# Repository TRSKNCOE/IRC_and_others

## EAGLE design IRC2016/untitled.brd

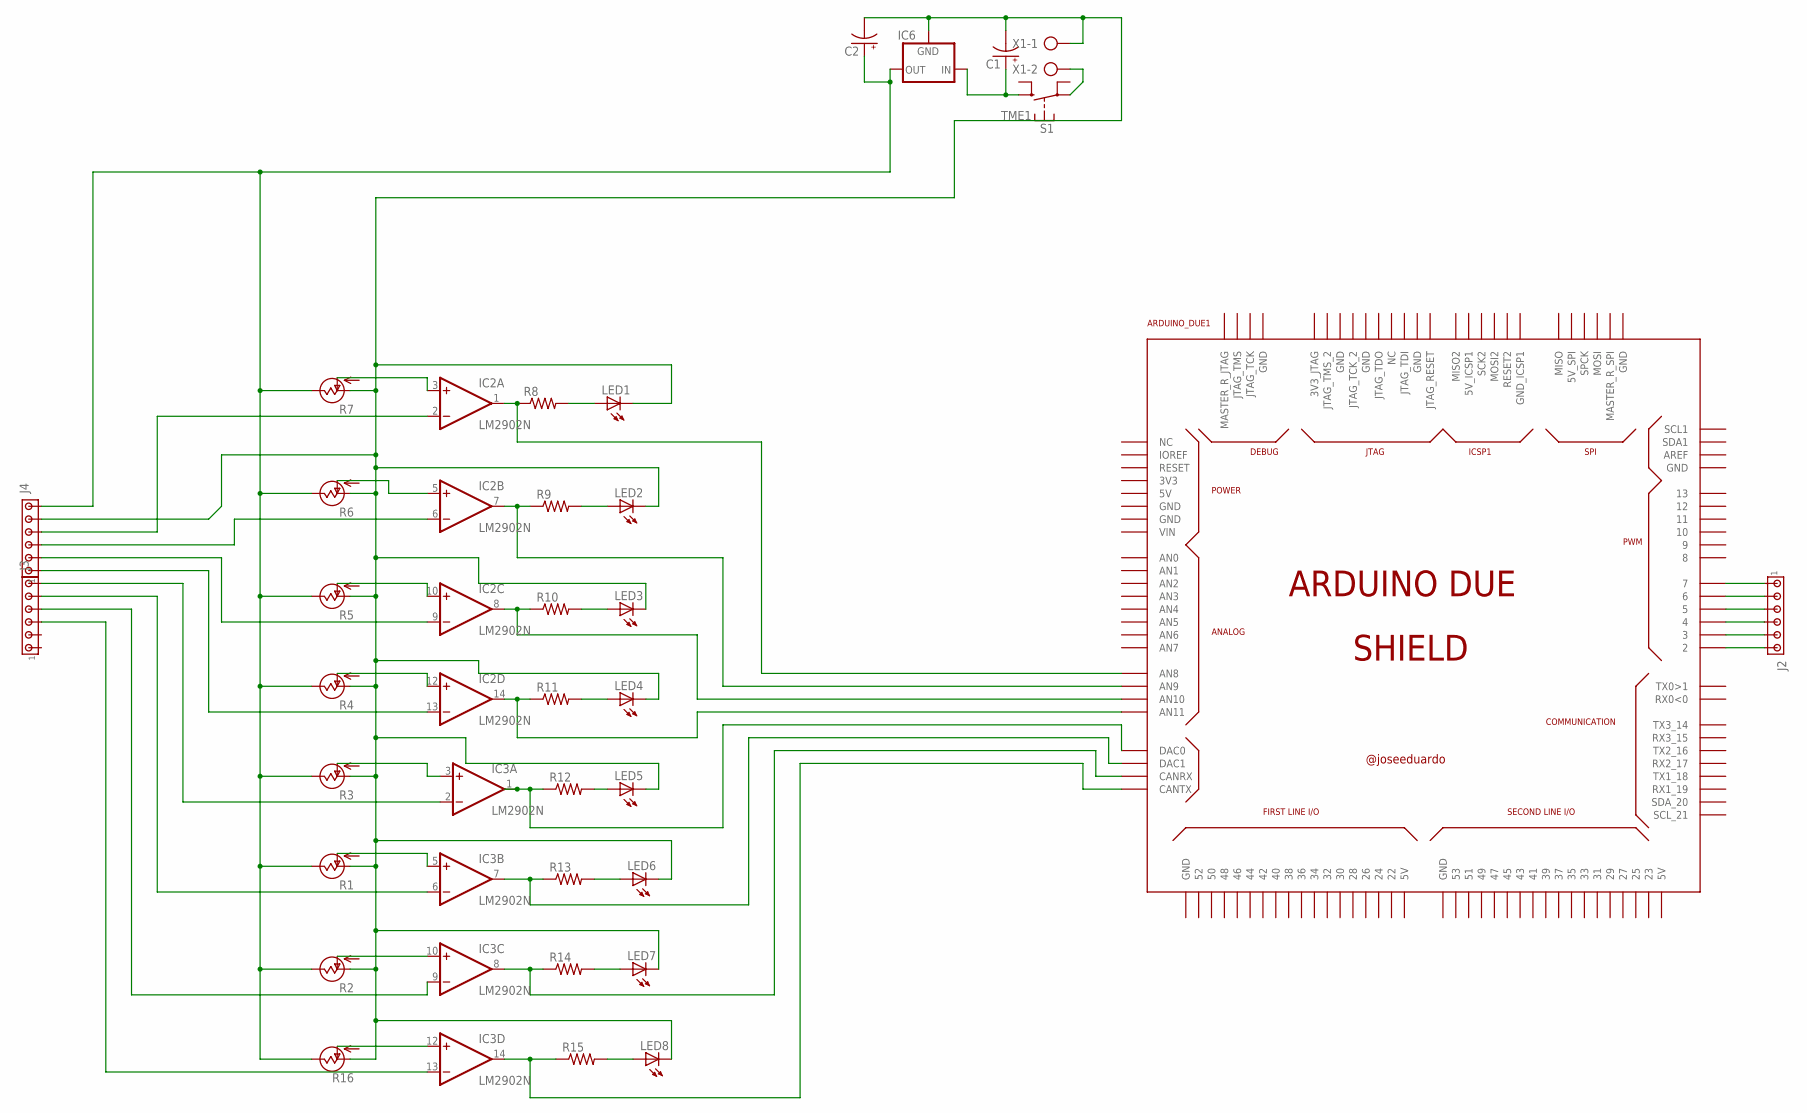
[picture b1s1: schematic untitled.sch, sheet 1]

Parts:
ARDUINO_DUE1: ARDUINO_DUE_SHIELD
C1, C2: CPOL-USE5-10.5; E5-10,5
IC2, IC3: LM2902N; DIL14
IC6: V_REG_78XXSIDE; 78XXL
J2, J3, J4: MTA06-156; 1X6MTA
LED1, LED2, LED3, LED4, LED5, LED6, LED7, LED8: LED3MM
R1, R2, R3, R4, R5, R6, R7, R16: POTTRS63P; S63P
R8, R9, R10, R11, R12, R13, R14, R15: R-US_0207/10; 0207/10
S1: TME1
X1: AK300/2

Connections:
unnamed: ARDUINO_DUE1.7, J2.1
unnamed: IC2.2 (-IN), J4.4
unnamed: ARDUINO_DUE1.6, J2.2
unnamed: IC2.6 (-IN), J4.3
unnamed: IC2.5 (+IN), R6.S (OUT)
unnamed: IC2.3 (+IN), R7.S (OUT)
unnamed: IC2.10 (+IN), R5.S (OUT)
unnamed: IC2.12 (+IN), R4.S (OUT)
unnamed: IC3.3 (+IN), R3.S (OUT)
unnamed: IC3.5 (+IN), R1.S (OUT)
unnamed: IC3.10 (+IN), R2.S (OUT)
unnamed: IC3.12 (+IN), R16.S (OUT)
unnamed: ARDUINO_DUE1.A8 (AN8), IC2.1 (OUT), R8.1
unnamed: LED1.A, R8.2
unnamed: ARDUINO_DUE1.A9 (AN9), IC2.7 (OUT), R9.1
unnamed: LED2.A, R9.2
unnamed: ARDUINO_DUE1.A10 (AN10), IC2.8 (OUT), R10.1
unnamed: LED3.A, R10.2
unnamed: ARDUINO_DUE1.A11 (AN11), IC2.14 (OUT), R11.1
unnamed: ARDUINO_DUE1.DAC0, IC3.1 (OUT), R12.1
unnamed: ARDUINO_DUE1.DAC1, IC3.7 (OUT), R13.1
unnamed: ARDUINO_DUE1.CANRX, IC3.8 (OUT), R14.1
unnamed: LED4.A, R11.2
unnamed: LED5.A, R12.2
unnamed: LED6.A, R13.2
unnamed: LED7.A, R14.2
unnamed: ARDUINO_DUE1.CANTX, IC3.14 (OUT), R15.1
unnamed: LED8.A, R15.2
unnamed: IC2.9 (-IN), J4.2
unnamed: ARDUINO_DUE1.5, J2.3
unnamed: IC2.13 (-IN), J4.1
unnamed: IC3.2 (-IN), J3.6
unnamed: IC3.6 (-IN), J3.5
unnamed: IC3.9 (-IN), J3.4
unnamed: ARDUINO_DUE1.4, J2.4
unnamed: ARDUINO_DUE1.3, J2.5
unnamed: ARDUINO_DUE1.2, J2.6
unnamed: IC3.13 (-IN), J3.3
unnamed: S1.2, X1.2
unnamed: C2.+, IC6.OUT, J4.6, R1.E (VSS), R2.E (VSS), R3.E (VSS), R4.E (VSS), R5.E (VSS), R6.E (VSS), R7.E (VSS), R16.E (VSS)
unnamed: C1.-, C2.-, IC6.GND, J4.5, LED1.K (C), LED2.K (C), LED3.K (C), LED4.K (C), LED5.K (C), LED6.K (C), LED7.K (C), LED8.K (C), R1.A (VDD), R2.A (VDD), R3.A (VDD), R4.A (VDD), R5.A (VDD), R6.A (VDD), R7.A (VDD), R16.A (VDD), X1.1
unnamed: C1.+, IC6.IN, S1.1 (S)
V+: IC2.4 (V+), IC3.4 (V+)
V-: IC2.11 (V-), IC3.11 (V-)

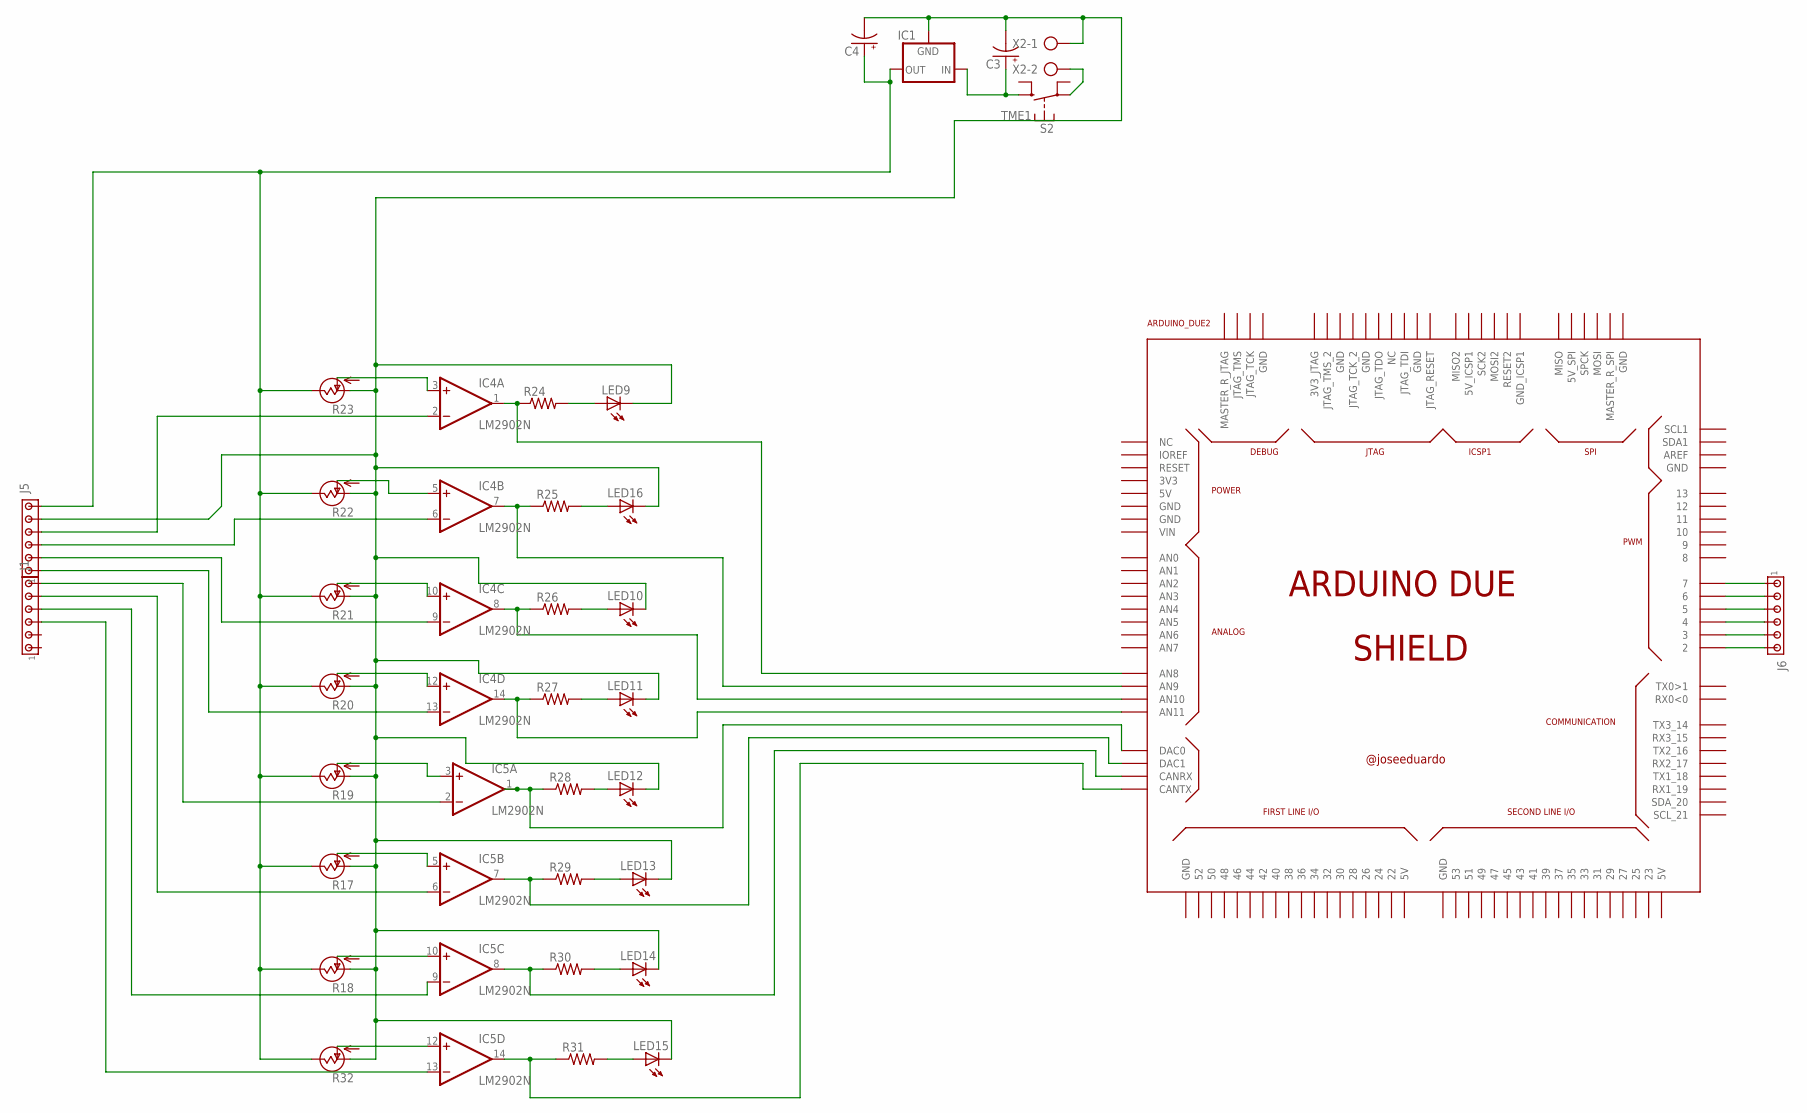
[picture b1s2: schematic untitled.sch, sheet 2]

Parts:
ARDUINO_DUE2: ARDUINO_DUE_SHIELD
C3, C4: CPOL-USE5-10.5; E5-10,5
IC1: V_REG_78XXSIDE; 78XXL
IC4, IC5: LM2902N; DIL14
J1, J5, J6: MTA06-156; 1X6MTA
LED9, LED10, LED11, LED12, LED13, LED14, LED15, LED16: LED3MM
R17, R18, R19, R20, R21, R22, R23, R32: POTTRS63P; S63P
R24, R25, R26, R27, R28, R29, R30, R31: R-US_0207/10; 0207/10
S2: TME1
X2: AK300/2

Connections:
unnamed: IC4.5 (+IN), R22.S (OUT)
unnamed: IC4.3 (+IN), R23.S (OUT)
unnamed: IC4.10 (+IN), R21.S (OUT)
unnamed: IC4.12 (+IN), R20.S (OUT)
unnamed: IC5.3 (+IN), R19.S (OUT)
unnamed: IC5.5 (+IN), R17.S (OUT)
unnamed: IC5.10 (+IN), R18.S (OUT)
unnamed: IC5.12 (+IN), R32.S (OUT)
unnamed: ARDUINO_DUE2.A8 (AN8), IC4.1 (OUT), R24.1
unnamed: ARDUINO_DUE2.A9 (AN9), IC4.7 (OUT), R25.1
unnamed: ARDUINO_DUE2.A10 (AN10), IC4.8 (OUT), R26.1
unnamed: LED10.A, R26.2
unnamed: ARDUINO_DUE2.A11 (AN11), IC4.14 (OUT), R27.1
unnamed: ARDUINO_DUE2.DAC0, IC5.1 (OUT), R28.1
unnamed: ARDUINO_DUE2.DAC1, IC5.7 (OUT), R29.1
unnamed: ARDUINO_DUE2.CANRX, IC5.8 (OUT), R30.1
unnamed: LED11.A, R27.2
unnamed: LED12.A, R28.2
unnamed: LED13.A, R29.2
unnamed: LED14.A, R30.2
unnamed: ARDUINO_DUE2.CANTX, IC5.14 (OUT), R31.1
unnamed: LED15.A, R31.2
unnamed: LED9.A, R24.2
unnamed: LED16.A, R25.2
unnamed: IC4.2 (-IN), J5.4
unnamed: IC4.6 (-IN), J5.3
unnamed: IC4.9 (-IN), J5.2
unnamed: IC4.13 (-IN), J5.1
unnamed: IC5.2 (-IN), J1.6
unnamed: IC5.6 (-IN), J1.5
unnamed: IC5.9 (-IN), J1.4
unnamed: IC5.13 (-IN), J1.3
unnamed: C4.+, IC1.OUT, J5.6, R17.E (VSS), R18.E (VSS), R19.E (VSS), R20.E (VSS), R21.E (VSS), R22.E (VSS), R23.E (VSS), R32.E (VSS)
unnamed: C3.-, C4.-, IC1.GND, J5.5, LED9.K (C), LED10.K (C), LED11.K (C), LED12.K (C), LED13.K (C), LED14.K (C), LED15.K (C), LED16.K (C), R17.A (VDD), R18.A (VDD), R19.A (VDD), R20.A (VDD), R21.A (VDD), R22.A (VDD), R23.A (VDD), R32.A (VDD), X2.1
unnamed: C3.+, IC1.IN, S2.1 (S)
unnamed: ARDUINO_DUE2.7, J6.1
unnamed: ARDUINO_DUE2.6, J6.2
unnamed: ARDUINO_DUE2.5, J6.3
unnamed: ARDUINO_DUE2.4, J6.4
unnamed: ARDUINO_DUE2.3, J6.5
unnamed: ARDUINO_DUE2.2, J6.6
unnamed: S2.2, X2.2
V+1: IC4.4 (V+), IC5.4 (V+)
V-1: IC4.11 (V-), IC5.11 (V-)

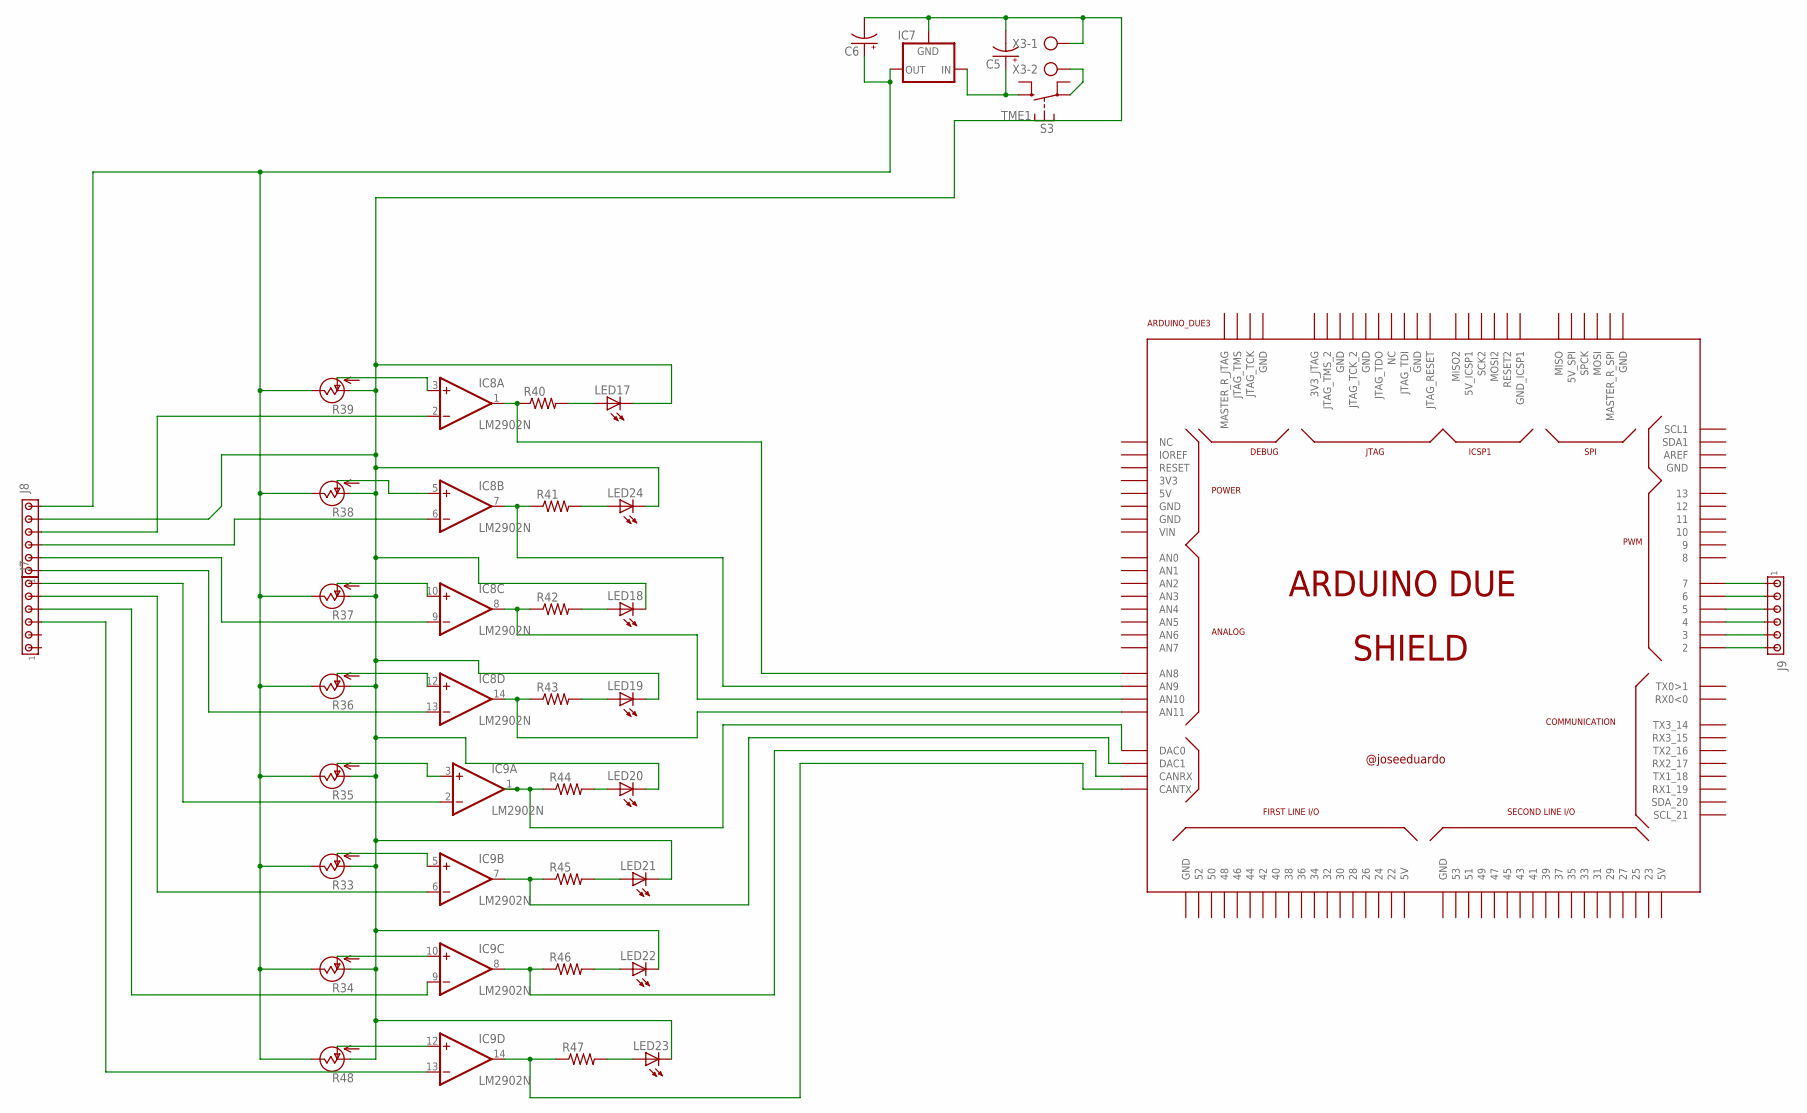
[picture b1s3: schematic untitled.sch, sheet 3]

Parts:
ARDUINO_DUE3: ARDUINO_DUE_SHIELD
C5, C6: CPOL-USE5-10.5; E5-10,5
IC7: V_REG_78XXSIDE; 78XXL
IC8, IC9: LM2902N; DIL14
J7, J8, J9: MTA06-156; 1X6MTA
LED17, LED18, LED19, LED20, LED21, LED22, LED23, LED24: LED3MM
R33, R34, R35, R36, R37, R38, R39, R48: POTTRS63P; S63P
R40, R41, R42, R43, R44, R45, R46, R47: R-US_0207/10; 0207/10
S3: TME1
X3: AK300/2

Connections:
unnamed: IC8.5 (+IN), R38.S (OUT)
unnamed: IC8.3 (+IN), R39.S (OUT)
unnamed: IC8.10 (+IN), R37.S (OUT)
unnamed: IC8.12 (+IN), R36.S (OUT)
unnamed: IC9.3 (+IN), R35.S (OUT)
unnamed: IC9.5 (+IN), R33.S (OUT)
unnamed: IC9.10 (+IN), R34.S (OUT)
unnamed: IC9.12 (+IN), R48.S (OUT)
unnamed: ARDUINO_DUE3.A8 (AN8), IC8.1 (OUT), R40.1
unnamed: ARDUINO_DUE3.A9 (AN9), IC8.7 (OUT), R41.1
unnamed: ARDUINO_DUE3.A10 (AN10), IC8.8 (OUT), R42.1
unnamed: LED18.A, R42.2
unnamed: ARDUINO_DUE3.A11 (AN11), IC8.14 (OUT), R43.1
unnamed: ARDUINO_DUE3.DAC0, IC9.1 (OUT), R44.1
unnamed: ARDUINO_DUE3.DAC1, IC9.7 (OUT), R45.1
unnamed: ARDUINO_DUE3.CANRX, IC9.8 (OUT), R46.1
unnamed: LED19.A, R43.2
unnamed: LED20.A, R44.2
unnamed: LED21.A, R45.2
unnamed: LED22.A, R46.2
unnamed: ARDUINO_DUE3.CANTX, IC9.14 (OUT), R47.1
unnamed: LED23.A, R47.2
unnamed: LED17.A, R40.2
unnamed: LED24.A, R41.2
unnamed: IC8.2 (-IN), J8.4
unnamed: IC8.6 (-IN), J8.3
unnamed: IC8.9 (-IN), J8.2
unnamed: IC8.13 (-IN), J8.1
unnamed: IC9.2 (-IN), J7.6
unnamed: IC9.6 (-IN), J7.5
unnamed: IC9.9 (-IN), J7.4
unnamed: IC9.13 (-IN), J7.3
unnamed: C6.+, IC7.OUT, J8.6, R33.E (VSS), R34.E (VSS), R35.E (VSS), R36.E (VSS), R37.E (VSS), R38.E (VSS), R39.E (VSS), R48.E (VSS)
unnamed: C5.-, C6.-, IC7.GND, J8.5, LED17.K (C), LED18.K (C), LED19.K (C), LED20.K (C), LED21.K (C), LED22.K (C), LED23.K (C), LED24.K (C), R33.A (VDD), R34.A (VDD), R35.A (VDD), R36.A (VDD), R37.A (VDD), R38.A (VDD), R39.A (VDD), R48.A (VDD), X3.1
unnamed: C5.+, IC7.IN, S3.1 (S)
unnamed: ARDUINO_DUE3.7, J9.1
unnamed: ARDUINO_DUE3.6, J9.2
unnamed: ARDUINO_DUE3.5, J9.3
unnamed: ARDUINO_DUE3.4, J9.4
unnamed: ARDUINO_DUE3.3, J9.5
unnamed: ARDUINO_DUE3.2, J9.6
unnamed: S3.2, X3.2
V+2: IC8.4 (V+), IC9.4 (V+)
V-2: IC8.11 (V-), IC9.11 (V-)

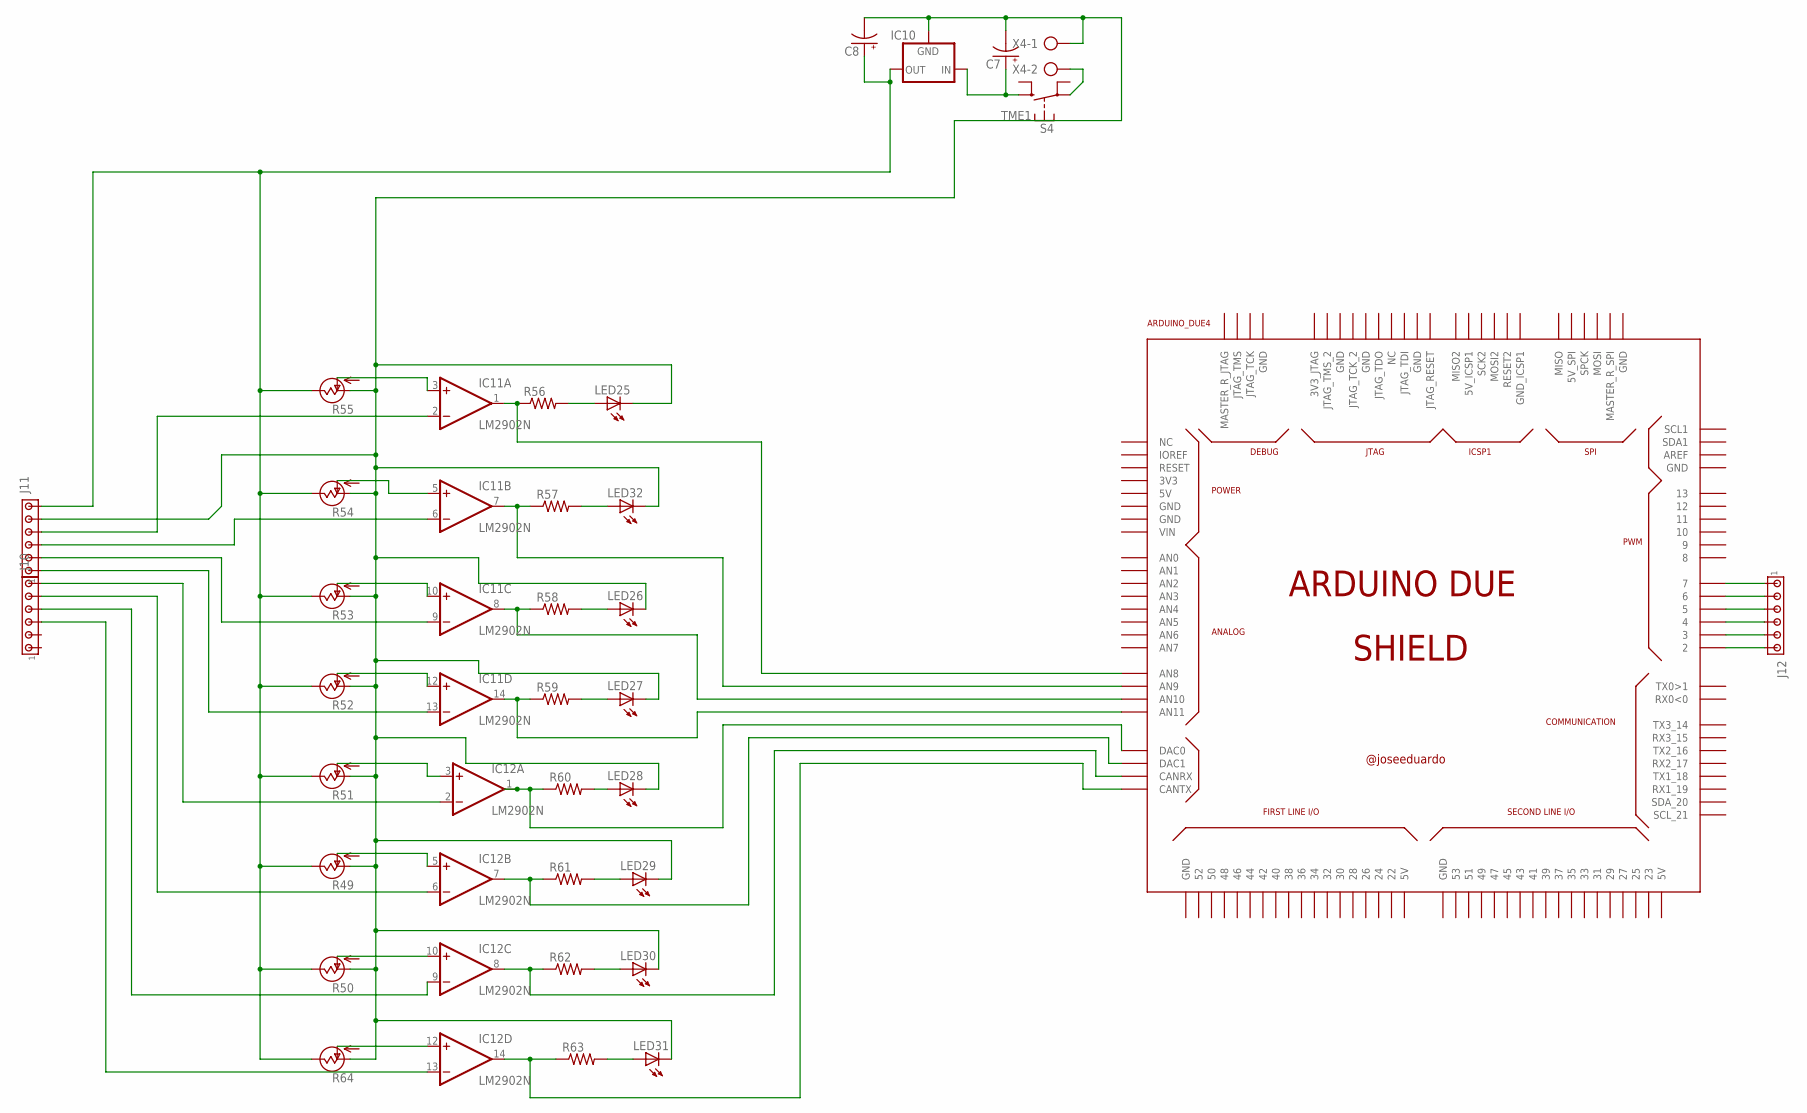
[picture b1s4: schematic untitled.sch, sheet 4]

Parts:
ARDUINO_DUE4: ARDUINO_DUE_SHIELD
C7, C8: CPOL-USE5-10.5; E5-10,5
IC10: V_REG_78XXSIDE; 78XXL
IC11, IC12: LM2902N; DIL14
J10, J11, J12: MTA06-156; 1X6MTA
LED25, LED26, LED27, LED28, LED29, LED30, LED31, LED32: LED3MM
R49, R50, R51, R52, R53, R54, R55, R64: POTTRS63P; S63P
R56, R57, R58, R59, R60, R61, R62, R63: R-US_0207/10; 0207/10
S4: TME1
X4: AK300/2

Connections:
unnamed: IC11.5 (+IN), R54.S (OUT)
unnamed: IC11.3 (+IN), R55.S (OUT)
unnamed: IC11.10 (+IN), R53.S (OUT)
unnamed: IC11.12 (+IN), R52.S (OUT)
unnamed: IC12.3 (+IN), R51.S (OUT)
unnamed: IC12.5 (+IN), R49.S (OUT)
unnamed: IC12.10 (+IN), R50.S (OUT)
unnamed: IC12.12 (+IN), R64.S (OUT)
unnamed: ARDUINO_DUE4.A8 (AN8), IC11.1 (OUT), R56.1
unnamed: ARDUINO_DUE4.A9 (AN9), IC11.7 (OUT), R57.1
unnamed: ARDUINO_DUE4.A10 (AN10), IC11.8 (OUT), R58.1
unnamed: LED26.A, R58.2
unnamed: ARDUINO_DUE4.A11 (AN11), IC11.14 (OUT), R59.1
unnamed: ARDUINO_DUE4.DAC0, IC12.1 (OUT), R60.1
unnamed: ARDUINO_DUE4.DAC1, IC12.7 (OUT), R61.1
unnamed: ARDUINO_DUE4.CANRX, IC12.8 (OUT), R62.1
unnamed: LED27.A, R59.2
unnamed: LED28.A, R60.2
unnamed: LED29.A, R61.2
unnamed: LED30.A, R62.2
unnamed: ARDUINO_DUE4.CANTX, IC12.14 (OUT), R63.1
unnamed: LED31.A, R63.2
unnamed: LED25.A, R56.2
unnamed: LED32.A, R57.2
unnamed: IC11.2 (-IN), J11.4
unnamed: IC11.6 (-IN), J11.3
unnamed: IC11.9 (-IN), J11.2
unnamed: IC11.13 (-IN), J11.1
unnamed: IC12.2 (-IN), J10.6
unnamed: IC12.6 (-IN), J10.5
unnamed: IC12.9 (-IN), J10.4
unnamed: IC12.13 (-IN), J10.3
unnamed: C8.+, IC10.OUT, J11.6, R49.E (VSS), R50.E (VSS), R51.E (VSS), R52.E (VSS), R53.E (VSS), R54.E (VSS), R55.E (VSS), R64.E (VSS)
unnamed: C7.-, C8.-, IC10.GND, J11.5, LED25.K (C), LED26.K (C), LED27.K (C), LED28.K (C), LED29.K (C), LED30.K (C), LED31.K (C), LED32.K (C), R49.A (VDD), R50.A (VDD), R51.A (VDD), R52.A (VDD), R53.A (VDD), R54.A (VDD), R55.A (VDD), R64.A (VDD), X4.1
unnamed: C7.+, IC10.IN, S4.1 (S)
unnamed: ARDUINO_DUE4.7, J12.1
unnamed: ARDUINO_DUE4.6, J12.2
unnamed: ARDUINO_DUE4.5, J12.3
unnamed: ARDUINO_DUE4.4, J12.4
unnamed: ARDUINO_DUE4.3, J12.5
unnamed: ARDUINO_DUE4.2, J12.6
unnamed: S4.2, X4.2
V+3: IC11.4 (V+), IC12.4 (V+)
V-3: IC11.11 (V-), IC12.11 (V-)

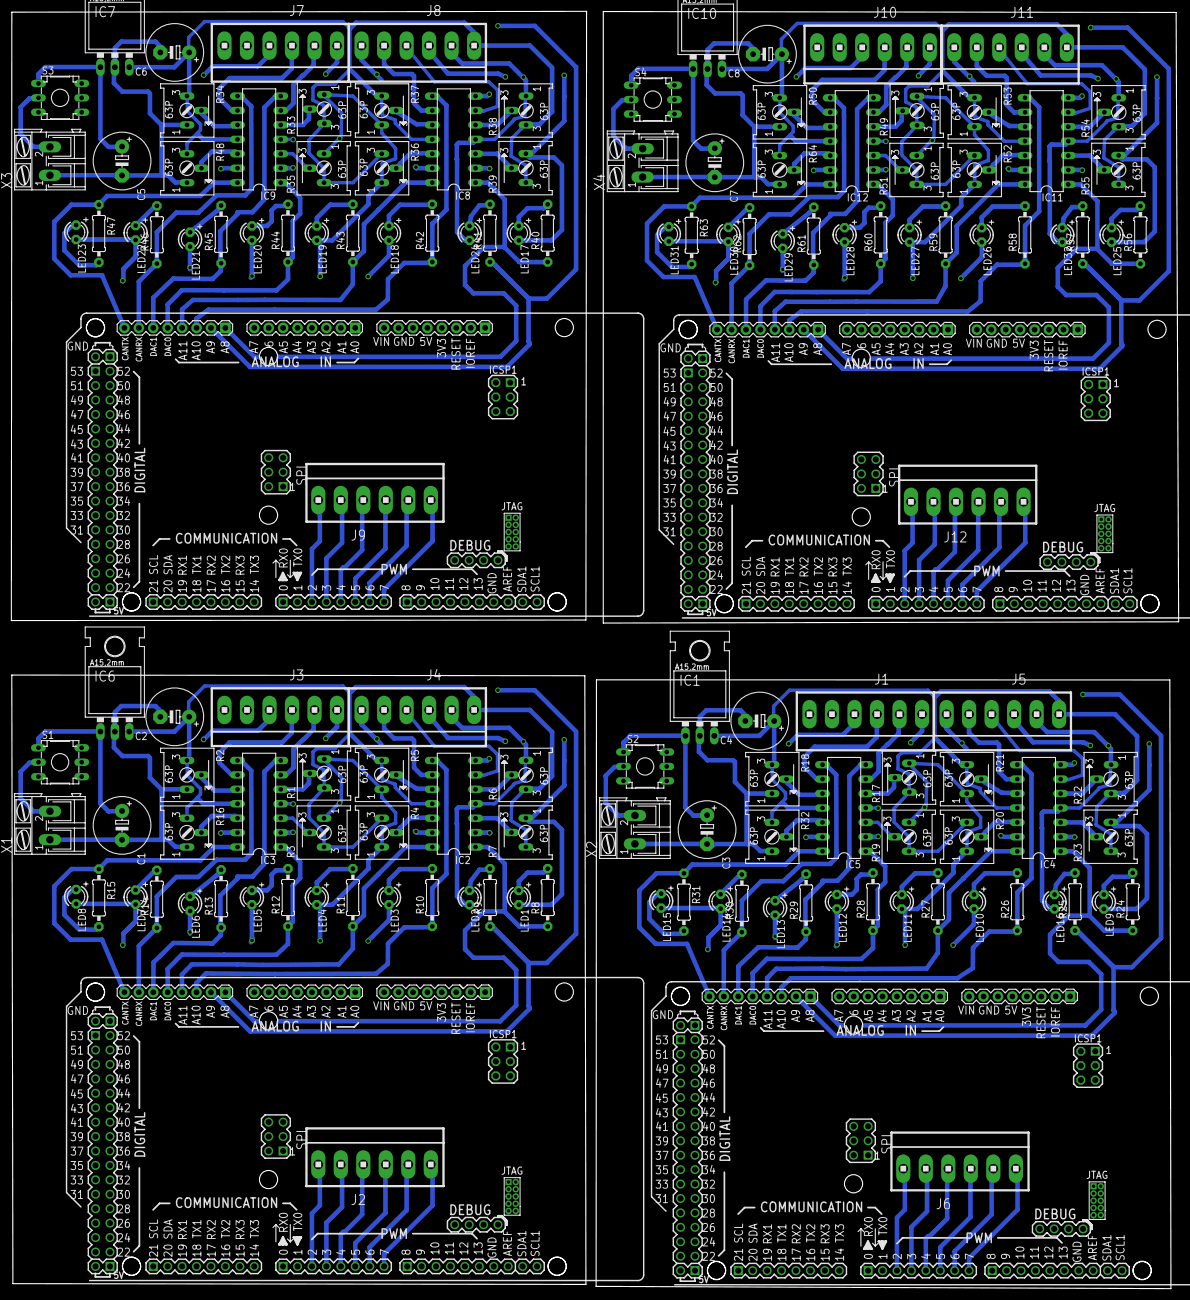
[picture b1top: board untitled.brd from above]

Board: 2 copper layers, 205.5 x 224.9 mm, 140 parts (0 on the bottom side), 176 nets.

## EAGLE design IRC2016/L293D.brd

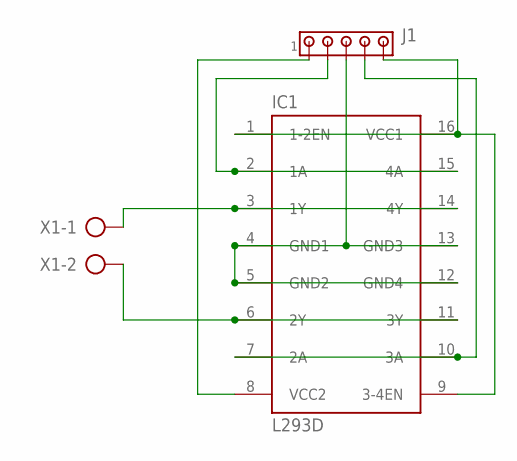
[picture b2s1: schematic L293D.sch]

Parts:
IC1: L293D; DIL16
J1: MTA05-100; 10X05MTA
X1: AK300/2

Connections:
unnamed: IC1.1 (1-2EN), IC1.9 (3-4EN), IC1.16 (VCC1), J1.5
unnamed: IC1.2 (1A), IC1.15 (4A), J1.2
unnamed: IC1.3 (1Y), IC1.14 (4Y), X1.1
unnamed: IC1.4 (GND1), IC1.5 (GND2), IC1.12 (GND4), IC1.13 (GND3), J1.3
unnamed: IC1.6 (2Y), IC1.11 (3Y), X1.2
unnamed: IC1.7 (2A), IC1.10 (3A), J1.4
unnamed: IC1.8 (VCC2), J1.1

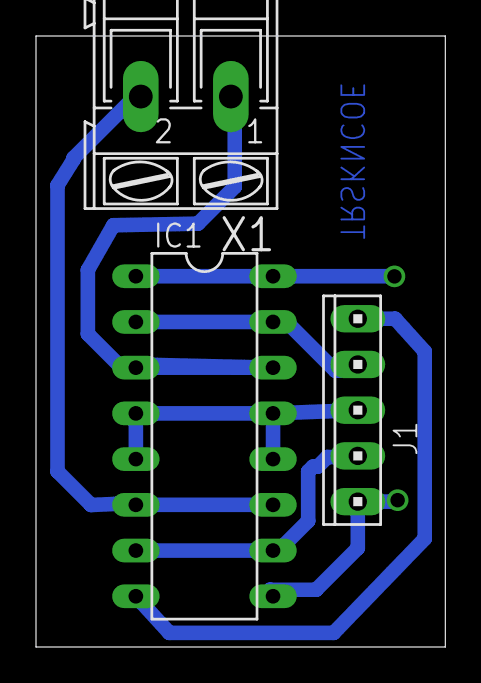
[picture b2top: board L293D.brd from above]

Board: 2 copper layers, 22.7 x 33.9 mm, 3 parts (0 on the bottom side), 7 nets.

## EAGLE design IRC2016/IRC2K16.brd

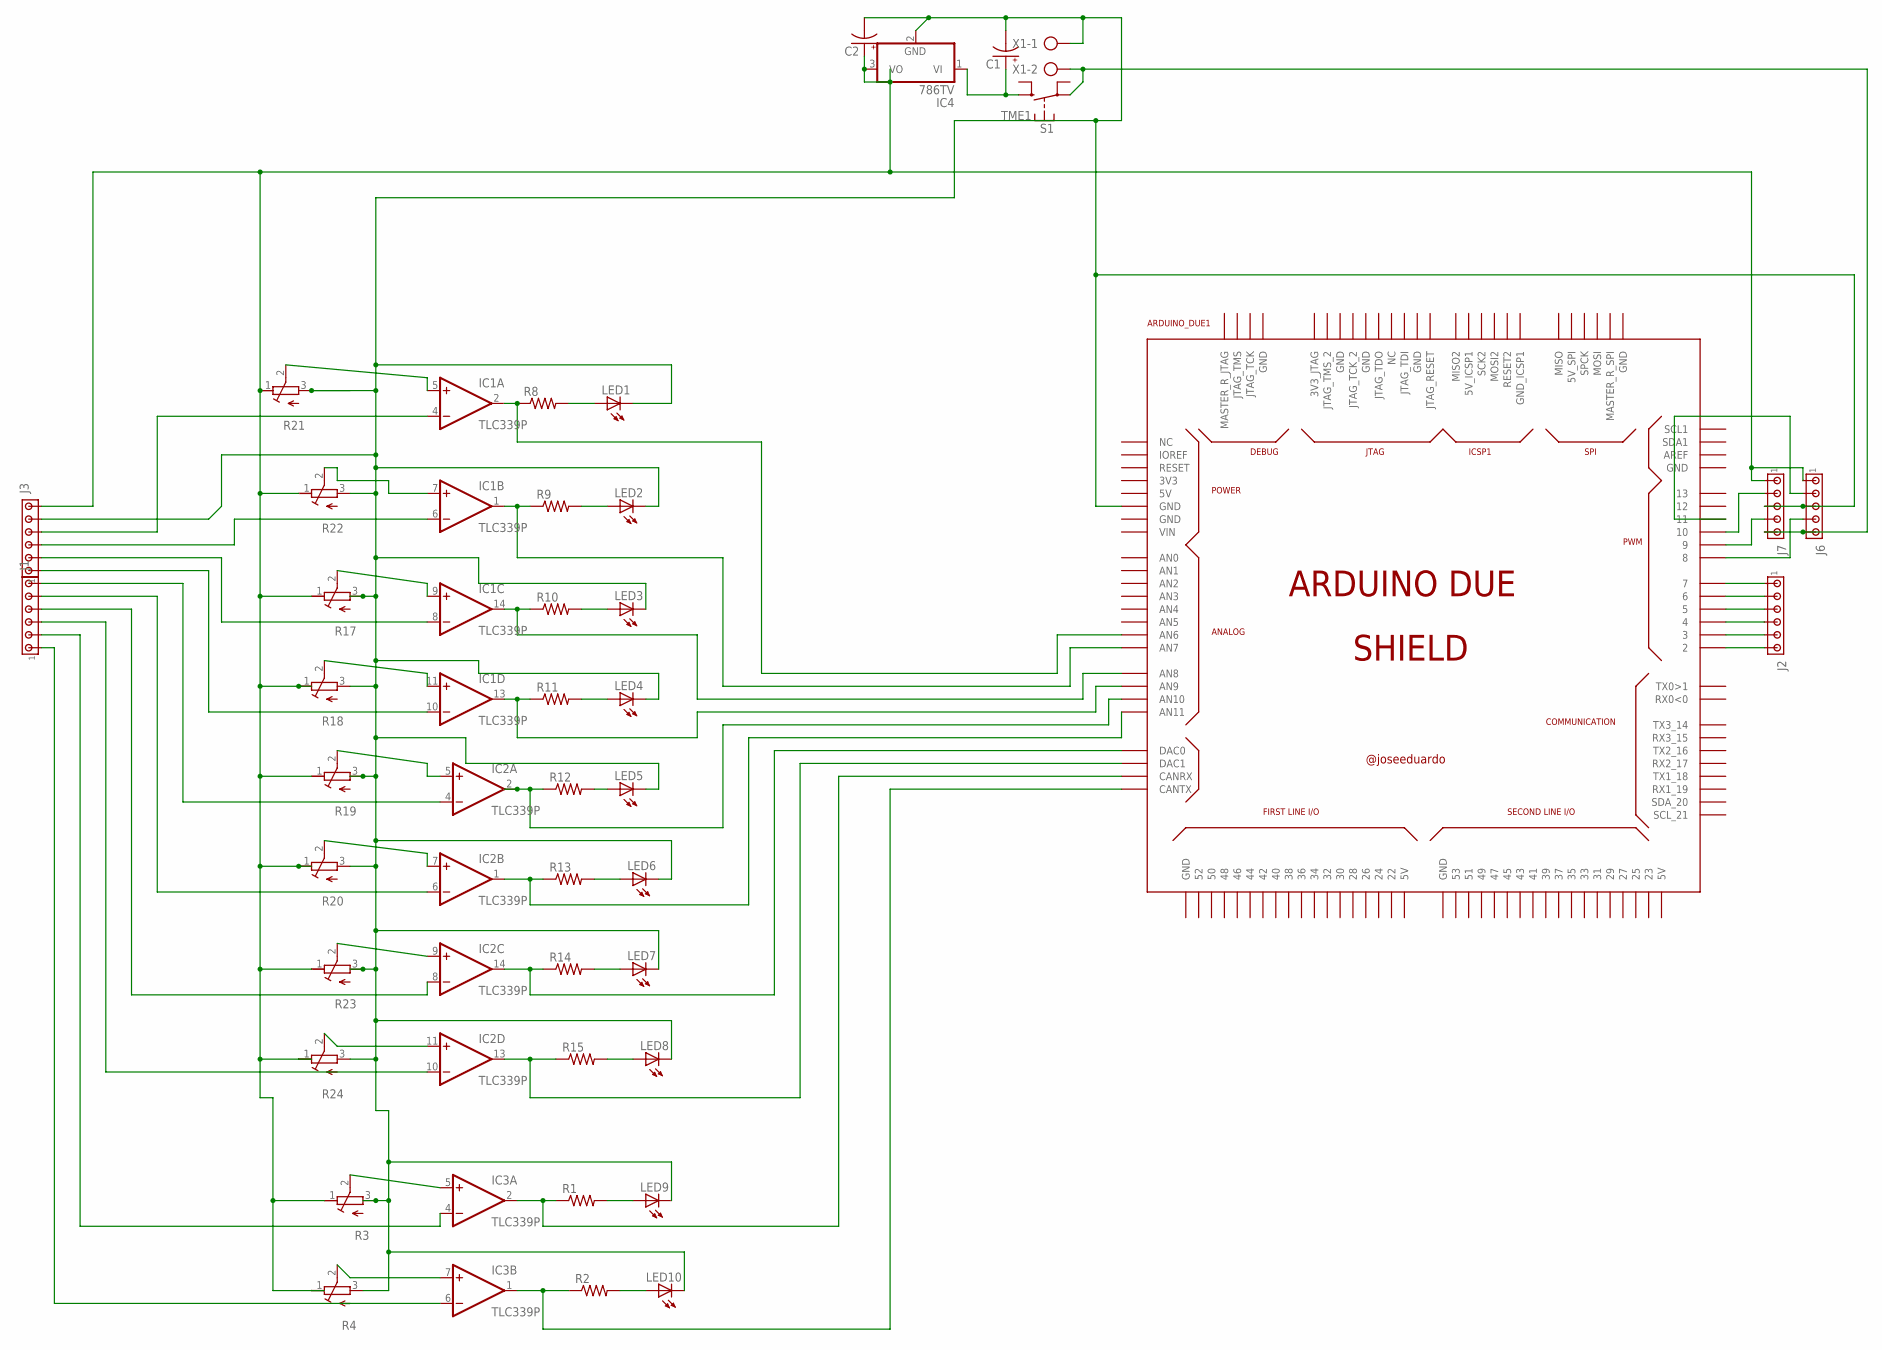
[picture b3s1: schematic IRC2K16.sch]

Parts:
ARDUINO_DUE1: ARDUINO_DUE_SHIELD
C1, C2: CPOL-USE5-10.5; E5-10,5
IC1, IC2, IC3: TLC339P; DIL14
IC4: 786TV; TO220V
J1, J2, J3: MTA06-100; 10X06MTA
J6, J7: MTA05-100; 10X05MTA
LED1, LED2, LED3, LED4, LED5, LED6, LED7, LED8, LED9, LED10: LED3MM
R1, R2, R8, R9, R10, R11, R12, R13, R14, R15: R-US_0207/10; 0207/10
R3, R4, R17, R18, R19, R20, R21, R22, R23, R24: R-TRIMMT93YA; RTRIMT93YA
S1: TME1
X1: AK300/2

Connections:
unnamed: ARDUINO_DUE1.7, J2.6 (1)
unnamed: IC1.4 (-IN), J3.3 (4)
unnamed: ARDUINO_DUE1.6, J2.5 (2)
unnamed: IC1.6 (-IN), J3.4 (3)
unnamed: IC1.7 (+IN), R22.2 (S)
unnamed: IC1.5 (+IN), R21.2 (S)
unnamed: IC1.9 (+IN), R17.2 (S)
unnamed: IC1.11 (+IN), R18.2 (S)
unnamed: IC2.5 (+IN), R19.2 (S)
unnamed: IC2.7 (+IN), R20.2 (S)
unnamed: IC2.9 (+IN), R23.2 (S)
unnamed: IC2.11 (+IN), R24.2 (S)
unnamed: ARDUINO_DUE1.A6 (AN6), IC1.2 (OUT), R8.1
unnamed: LED1.A, R8.2
unnamed: ARDUINO_DUE1.A7 (AN7), IC1.1 (OUT), R9.1
unnamed: LED2.A, R9.2
unnamed: ARDUINO_DUE1.A8 (AN8), IC1.14 (OUT), R10.1
unnamed: LED3.A, R10.2
unnamed: ARDUINO_DUE1.A9 (AN9), IC1.13 (OUT), R11.1
unnamed: ARDUINO_DUE1.A10 (AN10), IC2.2 (OUT), R12.1
unnamed: ARDUINO_DUE1.A11 (AN11), IC2.1 (OUT), R13.1
unnamed: ARDUINO_DUE1.DAC0, IC2.14 (OUT), R14.1
unnamed: LED4.A, R11.2
unnamed: LED5.A, R12.2
unnamed: LED6.A, R13.2
unnamed: LED7.A, R14.2
unnamed: ARDUINO_DUE1.DAC1, IC2.13 (OUT), R15.1
unnamed: LED8.A, R15.2
unnamed: IC1.8 (-IN), J3.5 (2)
unnamed: ARDUINO_DUE1.5, J2.4 (3)
unnamed: IC1.10 (-IN), J3.6 (1)
unnamed: IC2.4 (-IN), J1.1 (6)
unnamed: IC2.6 (-IN), J1.2 (5)
unnamed: IC2.8 (-IN), J1.3 (4)
unnamed: ARDUINO_DUE1.4, J2.3 (4)
unnamed: ARDUINO_DUE1.3, J2.2 (5)
unnamed: ARDUINO_DUE1.2, J2.1 (6)
unnamed: IC2.10 (-IN), J1.4 (3)
unnamed: J6.5, J7.5, S1.2, X1.2
unnamed: IC3.5 (+IN), R3.2 (S)
unnamed: ARDUINO_DUE1.8, J6.4
unnamed: IC3.7 (+IN), R4.2 (S)
unnamed: ARDUINO_DUE1.CANRX, IC3.2 (OUT), R1.1
unnamed: LED9.A, R1.2
unnamed: ARDUINO_DUE1.CANTX, IC3.1 (OUT), R2.1
unnamed: LED10.A, R2.2
unnamed: IC3.4 (-IN), J1.5 (2)
unnamed: IC3.6 (-IN), J1.6 (1)
unnamed: C2.+, IC4.3 (VO), J3.1 (6), J6.1, J7.1, R3.1 (A), R4.1 (A), R17.1 (A), R18.1 (A), R19.1 (A), R20.1 (A), R21.1 (A), R22.1 (A), R23.1 (A), R24.1 (A)
unnamed: ARDUINO_DUE1.GND, C1.-, C2.-, IC4.2 (GND), J3.2 (5), J6.3, J7.3, LED1.K (C), LED2.K (C), LED3.K (C), LED4.K (C), LED5.K (C), LED6.K (C), LED7.K (C), LED8.K (C), LED9.K (C), LED10.K (C), R3.3 (E), R4.3 (E), R17.3 (E), R18.3 (E), R19.3 (E), R20.3 (E), R21.3 (E), R22.3 (E), R23.3 (E), R24.3 (E), X1.1
unnamed: ARDUINO_DUE1.10, J7.2
unnamed: ARDUINO_DUE1.11, J6.2
unnamed: ARDUINO_DUE1.9, J7.4
unnamed: C1.+, IC4.1 (VI), S1.1 (S)
V+: IC1.3 (V+), IC2.3 (V+), IC3.3 (V+)
V-: IC1.12 (V-), IC2.12 (V-), IC3.12 (V-)

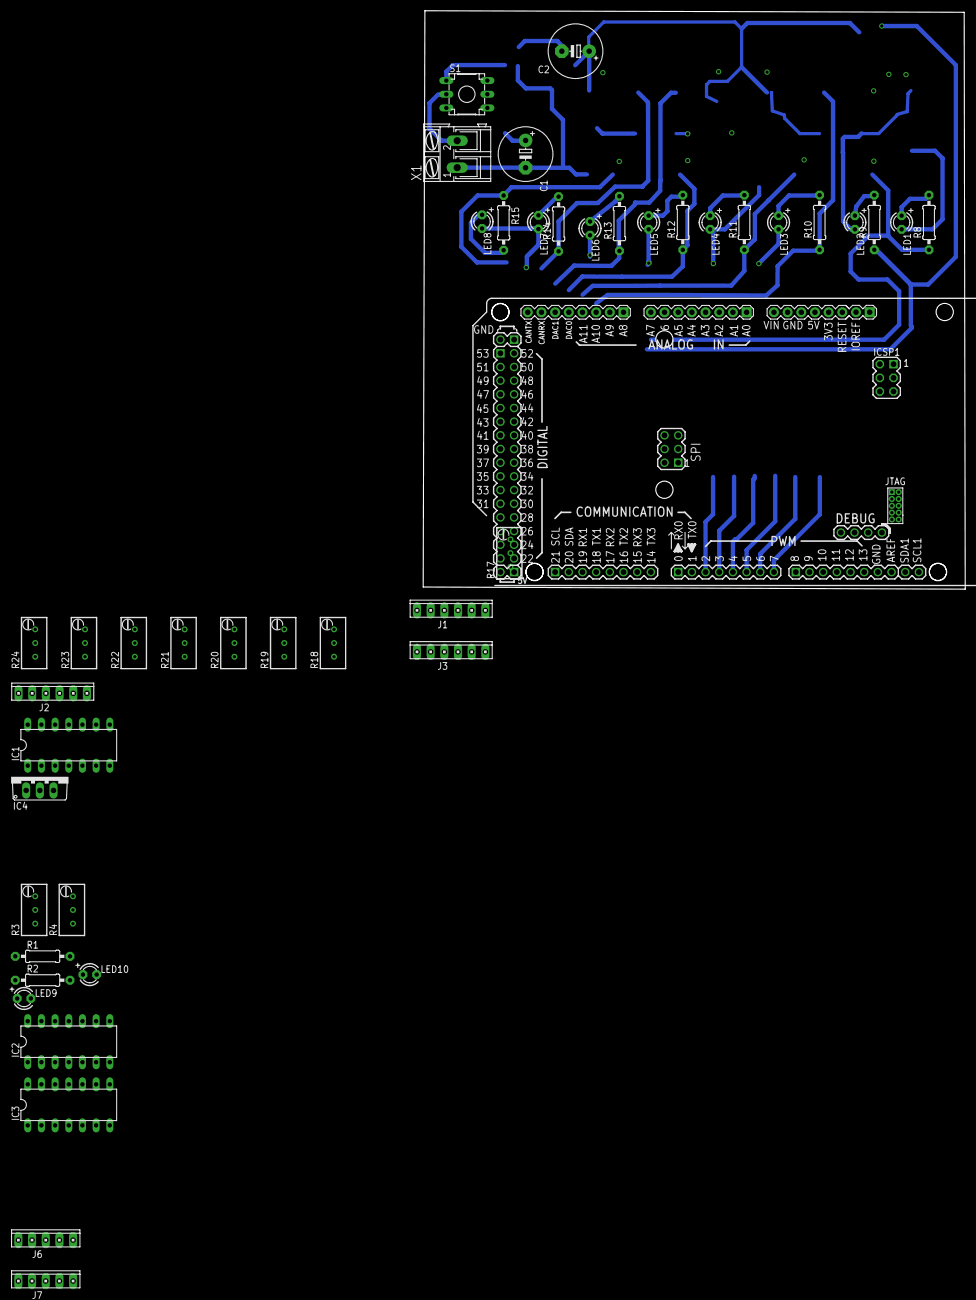
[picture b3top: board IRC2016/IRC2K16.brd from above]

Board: 2 copper layers, 100.7 x 107.4 mm, 44 parts (0 on the bottom side), 56 nets.
